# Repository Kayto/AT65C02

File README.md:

# AT65C02

**Latest News 15/12/2025**

**ATOS Software Released!** The main software suite for AT65C02 is now available in the Software_ATOS directory. ATOS (AT65C02 Operating System) provides a complete ROM-based monitor (SMON), interactive shell, trace/debugging commands, loadable program support, and integrated EhBASIC. The codebase has been extensively cleaned up and optimized with comprehensive documentation. This is now the recommended primary software for the AT65C02 platform.

**Hardware ideas 29/05/2025**

Picking up a few ideas for updates and improvements of the AT65C02.

1. How useful is the modem? Will i ever get around to testing this and integrating code? My vote is swinging to remove it. Opportunity to tidy the layout to better group a pinout for onboard rom programming.
2. I didn't add the possibility of using a MOS 6502! Looks like a simple jumper addition would allow this. 
3. The wireless UART doesnt have flow control - is there an alternative plug in wireless board that can provide this?
4. The HEX board resistor values...[sigh]!

**Previous News**
* **Minor fixes/additions to PCB to address some of the issues (see below revisions section).**
* **I am likely to pick up a futher revision 005 to address and consolidate some of the outstanding issues.**

## Introduction

Who doesn't want to build an 8 bit computer, if you don't, look away now.
I'm not a great coder or really an experienced maker but have enjoyed the magic of tinkering around with electronics since an early age. Whilst I have dabbled with 8 bit computing since the 80s, 40 years later I realise that I still do not really understand the inner workings of them. This project was to fill this knowledge gap.

Some of the best learning is obtained from example, making mistakes and getting your hands dirty. The only way for me is to actually break things down into individual steps, unpick the items then see how they all fit together and contribute.

I cant really credit myself with "designing" the AT65C02 - it borrows heavily from the work of others. However in breaking down these designs, incorporating changes and putting them together into my very own customised board, I have in many ways gained a much better understanding of how an 8 bit computer works. Result!

## Credits and thanks

Credits and thanks are worthy of being up front especially as I have leaned heavily on the work of others. Please follow the links to their respective documentation, they are far better at explaining and documenting than I can ever provide.

* <b>[Ben Eater's 8 bit computer](https://eater.net/8bit/)</b> \- the original inspiration\.
* <b>[Dawid Buchwald's](https://github.com/dbuchwald/6502)</b> DB6502 - this is brilliantly described and the designs form the basis for the AT65C02. The code examples and build environment are also the best for getting a solid base for coding. I recommend the github and [hackaday](https://hackaday.io/project/174128-db6502) report entries to really provide a deeper explanation of the design.
* <b>[Daryl Rictor](https://sbc.rictor.org/decoder.html)</b> \- for the DEC\-1 design\. The overall site also provides some great hobby computer examples\.
* <b>[AndersBNielsen](https://github.com/AndersBNielsen/SimpleModem)</b> for the "Simple Universal Modem" design.
* <b>[TEBL](https://github.com/tebl/C64-BlinkenDiag)</b> for the basis of the Blinkenlights.
* <b>[Michael Billington](https://github.com/mike42/6502-computer)</b> 65C02 computer - my first 65C02 build, super compact and a great starter for this journey.

## General Aims

* A 6502 build, as I am most familiar with this CPU and have at least a start at knowing some code and hardware requisities.
* Provide a learning platform for both the hardware and software. Ideally have a ready code base to get started with quickly.
* Avoid the hassles of masses of wiring and connections. To suit limited space, no mass of breadboards and able to tuck away in a cupboard to pick up quick.
* No great purist aspirations on the hardware, readily available components and no need to learn other code to get things running.

## Bespoke Aims

Some of these are really down to personal preference and perhaps held back a little by lack of knowledge.

* A load and save interface - to avoid pulling and burning ROMs every code example.
* Plenty of expansion - allows to tinker with interfacing displays and add ons.
* Wireless serial - the less wires the better.
* Adjustable memory decoder - because I can be indecisive and like to tinker.
* Blinkies - so I can get a real look at monitoring whats going on at an individual control signal, data and address line level.

## Final Features

In no particular order the main features in the final board are as follows.

* Onboard Step clock with manual and automatic tick. Speeds aprox 1-500Hz.
* Onboard 1mhz fixed clock.
* Seperate onboard serial clock.
* Blinky indicators - main signals, data and address, individual on/off switches.
* UART interface for external USB serial interface.
* ESP interface for wireless UART interface.
* Level shifter port for 5v and 3.3v signal conversion.
* Onboard 3.3v power regulator.
* Flexible IO and memory decoder via programable GAL. (this is now an add on board - it was too much to include on the same board).
* 2No VIAs - one for Keyboard, LCB and Blink LED - one spare for projects.
* Keyboard interface port (nice to have).
* LCD interface port.
* Onboard Blink LED (VIA1).
* VIA2 interface port.
* 4No. System Bus expansion interfaces (1No. via blinky latches).
* Modem audio interface.
* CPU extra signal breakout.
* LED brightness and LCD contrast adjusters - for late night blinky watching.
* Breakouts for ROM allow programming onboard via an Arduino or see below for ZIF option.
* Optional ZIF socket for ROM. Its a tight space but PCB ammended to accomodate the option of a ZIF socket at U8. **Please note that the ZIF socket interfers with the HEX expansion board. You will need a greater standoff to fit. The ZIF handle may also need shortening**.

## Memory Map

As will become clear when you tinker with 6502 builds, the hardware decisions up front impact the available memory size and locations.
Dawid Buchwald DB6502 provides a great explanation of the decisions around the choice of memory map and the differences with Ben Eater's design.
The default memory map for the AT65C02 is the same as DB6502 as follows.

| Segment | AT65C02 | Comment |
| ------- | ------- | ------- |
| RAM | 0x0000-0x7fff | 32K |
| VIA1 | 0x9000 | Connected to keyboard/LCD/blink LED |
| VIA2 | 0x8800 | VIA 2 port |
| ACIA | 0x8400 |  |
| ROM | 0xa000-0xffff | 24K First 8K of 32K ROM are not accessible |

Given I can be indecisive and to allow some experimentation with alternative memory maps I have included the option of switching to a programmable memory decoder. This uses the DEC-1 design by Daryl Rictor. The default DEC-1 map is as follows but with a bit of programming of the GALV22V10, you can experiment with other maps.

| Segment | DEC-1 | Comment |
| ------- | ----- | ------- |
| RAM | $0000-$01FF | zero page and stack space |
| IO Device #1 | $0200-$020F | (16 bytes) |
| IO Device #2 | $0210-$021F | (16 bytes) |
| IO Device #3 | $0220-$022F | (16 bytes) |
| IO Device #4 | $0230-$023F | (16 bytes) |
| Unassigned | $0240-$02FF |  |
| RAM | $0300-$7FFF | 32K |
| ROM | $8000-$FFFF | 32K |

## AT65C02 Build

The Final Rev004 PCB corrects the errors in my test builds. This first (Rev002) and second (Rev003) and third (Rev004) build was documented on [twitter](https://twitter.com/AdamT117). Feel free to check out those posts.

**Rev003 Spolier Alert** \- I had high hopes that Rev003 would be the final but alas things never work out as they should\, especially when learning\. Rev003 board undergoing testing\. ROM and VIA address decoding \- tested working\. RAM was troublesome\. I had a short between RAM OE and the RAM CS at the 74HC00 gates\. Oddly this was still there with all ICs unpopulated so must be a hidden short or trace damage\. The bare PCBs were ok\, so ruled that one out\. Given lack of time and parts I couldn't face another full build of a spare board\. Temporarily bodging the 74HC00 \(until i can find time to reassemble another board\)\, the Programmable memory decoder works when added to the dedicated expansion port\. Tested working alternative map with ROM at $8000\. OS/1 tested working via wireless serial add ons\. There is an issue on loading anything over 1K via wireless serial but this looks to be a software problem\.

**Rev002 Spolier alert** -The issues I found were mainly related to incorporating the adjustable address decoder. In trying to incorporate both a fixed and programmable GAL decoder I inadvertently bridged the RAM and ROM OE/CS lines. This was fixed with a trace cut and bodge but rendered the programmable memory decoder useless. Troubleshooting for the rev003 modifications involved temporary wires and jumpers. Other minor issues were silkscreen errors, this led me down a rabbit hole on a few occasions. The UART labels were mixed up, the level shifter pinout order was on the bottom of the board, the oscillator orientation was not clearly marked etc. I also took the opportunity to add in additional breakout headers for some unused CPU lines and for the ROM - allowing onboard ROM programming.

The repository provides the files for you to create your very own AT65C02.

* [Schematics](https://github.com/Kayto/blob/main/KiCad/Rev004/AT65C02_Schematic.pdf)
* [KiCad project files](https://github.com/Kayto/tree/main/KiCad/Rev004)
* [Gerber files](https://github.com/Kayto/tree/main/Gerbers)
* [BOM](https://github.com/Kayto/blob/main/KiCad/Rev004/AT_65C02_Computer_Rev004.csv)

### REVISION STATUS & ISSUES

**REV 004 - for final issue**

* Main board, Hex board and Programmable Memory Decoder Tested working.
* Modem - UNTESTED AT THE MOMENT

**Slight annoyances (which may or may not be investigated/fixed)**

* Hex board - for data FF the low F is very low brightness. It really needs some further balancing of the resistor values and grounding.
* Blinkies - Data lines have a bit of jitter with the clock. No biggie but OCD spotted it.
* Wireless Serial - using Xmodem is fine with very small code uploads but the larger files fail. Workaround is to use a wired serial. I am hoping this can be helped with code but might wait until I can acquire the skills to troubleshoot! **Update 06/2024. Rather stupidly I forgot that the ESP-01 does not have flow control. Therefore anything bigger than the buffer (like large file transfers) fails. The ESP-01 therefore provides a useful serial input but its use is limited.**
* Wired UART Interface - Silkscreen RTS and CTS need swapping. Bit of a mistake as I was looking at a direct FTDI plug in. As FTDI programmers vary its no big issue to use jumper wires. **Fixed 08/2023**.
* Wireless or wired serial switching - would have been nice to have a jumper to switch out the wireless ESP-01 module rather than unplugging. **Fixed 08/2023**.
* Breakouts for x2 spare level shifter channels. **Fixed 08/2023**.
* Standardise some headers to even sizes. **Fixed 08/2023**.

## JUMPERS

There are a number of jumpers/headers on the PCB which may need some explanation?
I have created a separate page [here](https://github.com/Kayto/blob/main/Jumpers.md) to explain them.

## Software

### ATOS - Primary Software Suite (RECOMMENDED)

**[Software_ATOS](https://github.com/Kayto/AT65C02/tree/main/Software/Software%20_ATOS)** is the main firmware and software suite for the AT65C02. It provides a complete operating environment with ROM-based SMON monitor, interactive shell, comprehensive debugging tools, and loadable program support.

**Key Features:**
- ROM-based SMON monitor with full debugging capabilities
- Interactive shell with command history
- Trace commands: single-step (TW), breakpoints (TB), run-to-address (TQ/TS)
- Loadable program support via Intel HEX format
- Integrated EhBASIC interpreter
- LCD and serial I/O drivers
- Multiple UART support (6551, 6522, 6850)
- Complete build system using Docker (cc65 toolchain)
- VS Code integration with build tasks

**Quick Start:**
```bash
cd Software_ATOS
docker run --rm -v '${PWD}:/mnt/project' dawidbuchwald/cc65-tools-make all
```

See the [ATOS README]([Software_ATOS](https://github.com/Kayto/AT65C02/tree/main/Software/Software%20_ATOS)/README.md) for complete documentation.

### Alternative Software Options

As stated earlier Dawid Buchwald provides a suite of ROM and loadable sources in his github repo. This will get you on your way to coding quickly. If you are struggling with a build environment then he also has great tutorial examples and even provides a [docker image](https://github.com/dbuchwald/cc65-tools), great work.

I am trying to avoid duplication of the original code repos so where possible will only include the new or revised code. Please check the original author licence included in the folders and in the acknowledgments.

| Reference | Description | Credit |
| --------- | ----------- | ------ |
| **[50\_mem\_read](https://github.com/Kayto/tree/main/Software/50_mem_read)** | RAM test, VIA1 and VIA 2 test blinks | by me - needs to be combined with the DB6502 repo for compilation. |
| **[sbc2os](https://github.com/Kayto/tree/main/Software/sbc2os)** | I include here the revised TASS source as it needed changes for the default AT65C02 memory map. A binary is also included for those who may struggle with TASS. | Original by [Daryl Rictor](https://sbc.rictor.org/sbcos.html). The original author README is included. |
| **[EhBasic](https://github.com/Kayto/tree/main/Software/EhBasic)** | Using the DB6502 docker image for compilation | Refer to the included [license](https://github.com/Kayto/blob/main/Software/EhBasic/LICENSE) file. |
| **[smon6502](https://github.com/Kayto/tree/main/Software/smon6502)** | [dhansel smon6502](https://github.com/dhansel/smon6502) Using the DB6502 VASM docker image for compilation. | Refer to the included [Readme](https://github.com/Kayto/blob/main/Software/smon6502/readme.md) file. |
| **[sysmon65](https://github.com/Kayto/tree/main/Software/SYSMON65-main)** | [jdimeglio sysmon65](https://github.com/jdimeglio/SYSMON65) | Binary only ATM. Will include the relevant modified source files shortly. Use original source and replace files that have been modified. Compilation requires the Michal Kowalski assembler/simulator |

The only other code requirement is for the ATTiny4313, for the onboard keyboard controller. An explanation of this is in the [Arduino](https://github.com/Kayto/tree/main/Software/Arduino) folder.

## Expansion

### Hex Board

Gerbers and KiCad is provided in this repo for an expansion board. This PCB plugs into the expansion port next to the blinkies. It provides hexidecmal display output aligned with the blinkenlights. Look in the software folder for the .jed files for programming the GALs.

### Programmable IO and memory decoder

This is now a seperate PCB that plugs into the relevant marked ports. Gerbers and KiCad provided. Allows tinkering with IO and memory maps. The design is based on the DEC-1 so refer to the links to Daryl Rictor's site for the .jed file for the GAL.

## Future Expansion

I have a number of aspirations for future expansion boards which are part way into development or at least have me thinking about. Most will rely on code development so really have no fixed date for release.

#### Floppy Drive controller

Allowing connection and control of a 5.25inch floppy disc drive. There are a few existing examples by some clever folk that could be adapted for use. I envisage a vertical board into an expansion slot - there are also plenty of additional breakouts on the AT65C02 that could be jumper wired if needed. A connector on an expansion board is not that robust. I thought of providing space for a DIN connector on the main board to serve this future item - but will save as just an idea for now.

#### Case

This could be an easy one as by some fluke the board size seems to fit some IKEA storage boxes I use. Most of the switches used on the board can be jumpered as I have used header pins. Similarily any expansion could be wired up too.

#### Debugger Plug-in

**Coming Soon -** A plug in board to allow degugging and onboard ROM programming via an Arduino.

## Licenses & acknowledgement

Further to the links in the credit section.
The design is an extension of Ben Eater's 6502 computer tutorial, which is itself based on the work of the 6502.org community.

**6502 KiCad Library**

The PCB files use modified versions of the 6502 KiCad Library. Copyright 2018, Nicholas Parks Young. All Rights Reserved. The 6502 KiCad Library library is licensed under the GNU LGPL v2.1

**EhBASIC**

With the exception of the files noted below, code base © 2021 Michael Billington, and is licensed under a Creative Commons Attribution 4.0 International License.
The files in EhBasic/basic/ are derived from EhBASIC, developed by Lee Davidson. The EhBASIC license allows for non-commerical use only. The most recent release and manual is hosted here, and a mirror of Lee's website can be found here.

EhBASIC is free but not copyright free. For non commercial use there is only one restriction, any derivative work should include, in any binary image distributed, the string "Derived from EhBASIC" and in any distribution that includes human readable files a file that includes the above string in a human readable form e.g. not as a comment in an HTML file.

**DB6502 Code**

OS/1, related code examples and Arduino code is Copyright (c) 2020 Dawid Buchwald and is licensed under a MIT License.

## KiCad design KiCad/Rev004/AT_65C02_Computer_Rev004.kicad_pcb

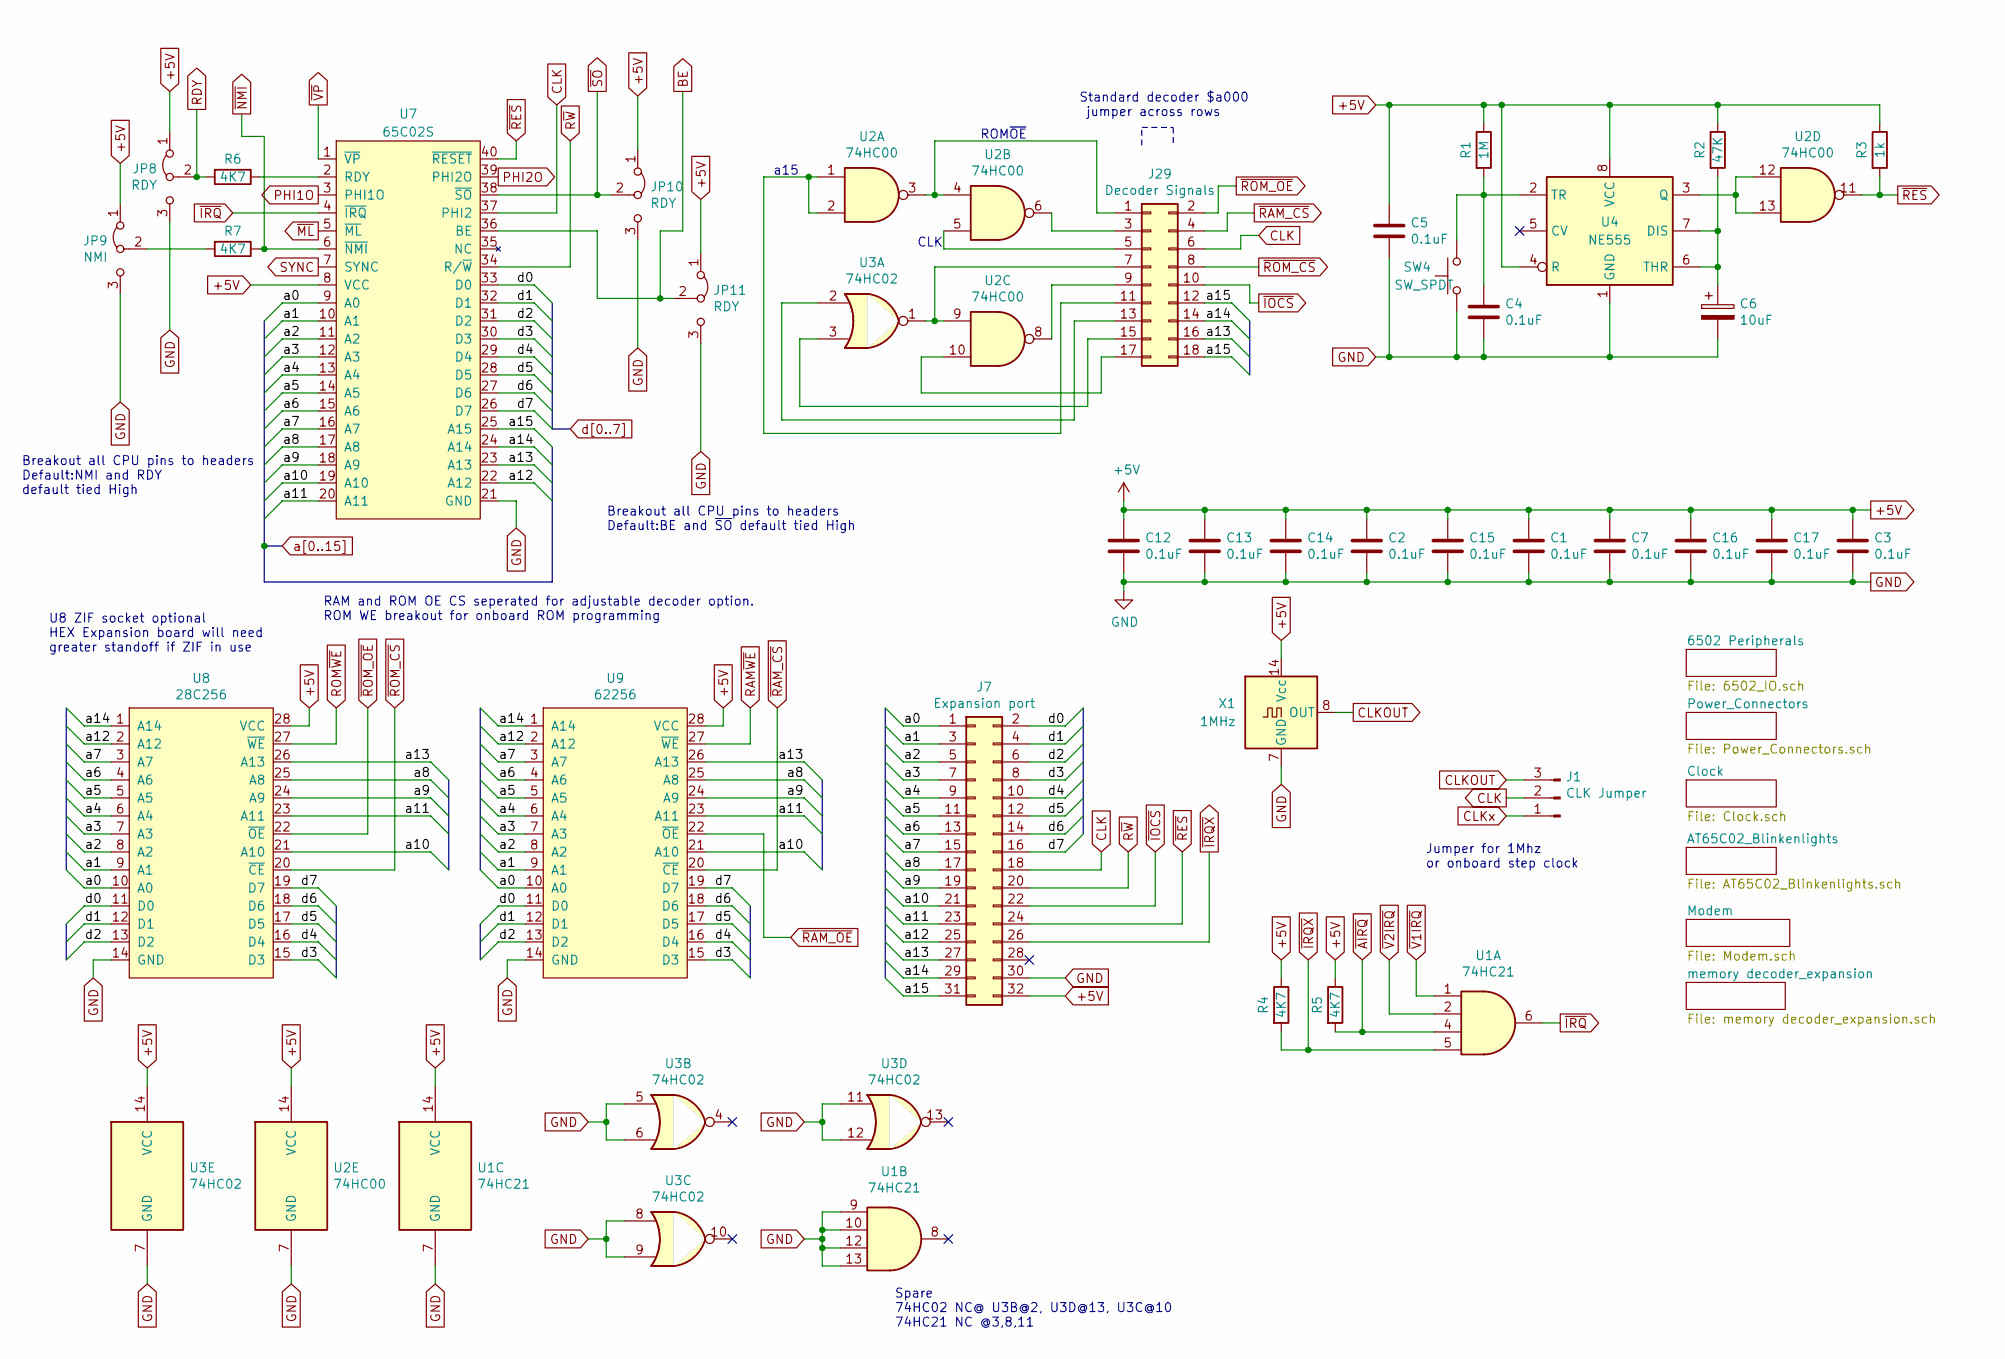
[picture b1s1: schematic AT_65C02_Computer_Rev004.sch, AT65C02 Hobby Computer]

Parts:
C1, C2, C3, C4, C5, C7, C12, C13, C14, C15, C16, C17: 0.1uF; C_Disc_D3.4mm_W2.1mm_P2.50mm
C6: 10uF; CP_Radial_D5.0mm_P2.50mm
J1: CLK Jumper; PinHeader_1x03_P2.54mm_Vertical
J7: Expansion port; PinSocket_2x16_P2.54mm_Vertical
J29: Decoder Signals; PinHeader_2x09_P2.54mm_Vertical
JP8, JP10, JP11: RDY; PinHeader_1x03_P2.54mm_Vertical
JP9: NMI; PinHeader_1x03_P2.54mm_Vertical
R1: 1M; R_Axial_DIN0207_L6.3mm_D2.5mm_P7.62mm_Horizontal
R2: 47K; R_Axial_DIN0207_L6.3mm_D2.5mm_P7.62mm_Horizontal
R3: 1k; R_Axial_DIN0207_L6.3mm_D2.5mm_P7.62mm_Horizontal
R4, R5, R6, R7: 4K7; R_Axial_DIN0207_L6.3mm_D2.5mm_P7.62mm_Horizontal
SW4: SW_SPDT; SW_PUSH_6mm
U1: 74HC21; DIP-14_W7.62mm_Socket
U2: 74HC00; DIP-14_W7.62mm_Socket
U3: 74HC02; DIP-14_W7.62mm_Socket
U4: NE555; DIP-8_W7.62mm_Socket
U7: 65C02S; DIP-40_W15.24mm_Socket
U8: 28C256; DIP_Socket-28_W11.9_W12.7_W15.24_W17.78_W18.5_3M_228-1277-0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
U9: 62256; DIP-28_W15.24mm_Socket
X1: 1MHz; Oscillator_DIP-14

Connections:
BE: JP11.2 (C), U7.36 (BE); also elsewhere on the board
CLK: J1.2, J7.18, J29.6, U7.37 (PHI2); also elsewhere on the board
CLKOUT: J1.3, X1.8 (OUT)
CLKx: J1.1; also elsewhere on the board
unnamed: C4.1, R1.2, SW4.2, U4.2 (TR)
unnamed: C6.1, R2.2, U4.6 (THR), U4.7 (DIS)
unnamed: J29.1, U2.3, U2.4
unnamed: J29.3, U2.6
unnamed: J29.5, U2.5
unnamed: J29.7, U2.9, U3.1
unnamed: J29.9, U2.8
unnamed: J29.11, U2.1, U2.2
unnamed: J29.13, U3.2
unnamed: J29.15, U3.3
unnamed: J29.17, U2.10
unnamed: JP9.2 (C), R7.2
unnamed: R6.1, U7.2 (RDY)
unnamed: U2.12, U2.13, U4.3 (Q)
PHI1O: U7.3 (PHI1O); also elsewhere on the board
PHI2O: U7.39 (PHI2O); also elsewhere on the board
RAM~WE~: U9.27 (~WE); also elsewhere on the board
RDY: JP8.2 (C), R6.2; also elsewhere on the board
ROM~WE: U8.27 (~WE); also elsewhere on the board
R~W: J7.20, U7.34 (R/~W); also elsewhere on the board
SYNC: U7.7 (SYNC); also elsewhere on the board
a0: J7.1, U7.9 (A0), U8.10 (A0), U9.10 (A0); also elsewhere on the board
a1: J7.3, U7.10 (A1), U8.9 (A1), U9.9 (A1); also elsewhere on the board
a2: J7.5, U7.11 (A2), U8.8 (A2), U9.8 (A2); also elsewhere on the board
a3: J7.7, U7.12 (A3), U8.7 (A3), U9.7 (A3); also elsewhere on the board
a4: J7.9, U7.13 (A4), U8.6 (A4), U9.6 (A4); also elsewhere on the board
a5: J7.11, U7.14 (A5), U8.5 (A5), U9.5 (A5); also elsewhere on the board
a6: J7.13, U7.15 (A6), U8.4 (A6), U9.4 (A6); also elsewhere on the board
a7: J7.15, U7.16 (A7), U8.3 (A7), U9.3 (A7); also elsewhere on the board
a8: J7.17, U7.17 (A8), U8.25 (A8), U9.25 (A8); also elsewhere on the board
a9: J7.19, U7.18 (A9), U8.24 (A9), U9.24 (A9); also elsewhere on the board
a10: J7.21, U7.19 (A10), U8.21 (A10), U9.21 (A10); also elsewhere on the board
a11: J7.23, U7.20 (A11), U8.23 (A11), U9.23 (A11); also elsewhere on the board
a12: J7.25, U7.22 (A12), U8.2 (A12), U9.2 (A12); also elsewhere on the board
a13: J7.27, J29.16, U7.23 (A13), U8.26 (A13), U9.26 (A13); also elsewhere on the board
a14: J7.29, J29.14, U7.24 (A14), U8.1 (A14), U9.1 (A14); also elsewhere on the board
a15: J7.31, J29.12, J29.18, U7.25 (A15); also elsewhere on the board
d0: J7.2, U7.33 (D0), U8.11 (D0), U9.11 (D0); also elsewhere on the board
d1: J7.4, U7.32 (D1), U8.12 (D1), U9.12 (D1); also elsewhere on the board
d2: J7.6, U7.31 (D2), U8.13 (D2), U9.13 (D2); also elsewhere on the board
d3: J7.8, U7.30 (D3), U8.15 (D3), U9.15 (D3); also elsewhere on the board
d4: J7.10, U7.29 (D4), U8.16 (D4), U9.16 (D4); also elsewhere on the board
d5: J7.12, U7.28 (D5), U8.17 (D5), U9.17 (D5); also elsewhere on the board
d6: J7.14, U7.27 (D6), U8.18 (D6), U9.18 (D6); also elsewhere on the board
d7: J7.16, U7.26 (D7), U8.19 (D7), U9.19 (D7); also elsewhere on the board
~AIRQ: R5.2, U1.4; also elsewhere on the board
~IOCS: J7.22, J29.10; also elsewhere on the board
~IRQ: U1.6, U7.4 (~IRQ); also elsewhere on the board
~IRQX: J7.26, R4.2, U1.5; also elsewhere on the board
~ML: U7.5 (~ML); also elsewhere on the board
~NMI: R7.1, U7.6 (~NMI); also elsewhere on the board
~RAM_CS: J29.4, U9.20 (~CE); also elsewhere on the board
~RAM_OE: U9.22 (~OE); also elsewhere on the board
~RES: J7.24, R3.2, U2.11, U7.40 (~RESET); also elsewhere on the board
~ROM_CS: J29.8, U8.20 (~CE); also elsewhere on the board
~ROM_OE: J29.2, U8.22 (~OE); also elsewhere on the board
~SO: JP10.2 (C), U7.38 (~SO); also elsewhere on the board
~V1IRQ: U1.1; also elsewhere on the board
~V2IRQ: U1.2; also elsewhere on the board
~VP: U7.1 (~VP); also elsewhere on the board

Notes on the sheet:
Breakout all CPU pins to headers Default:NMI and RDY default tied High
RAM and ROM OE CS seperated for adjustable decoder option. ROM WE breakout for onboard ROM programming
Jumper for 1Mhz or onboard step clock
Spare 74HC02 NC@ U3B@2, U3D@13, U3C@10 74HC21 NC @3,8,11
Standard decoder $a000 jumper across rows
Breakout all CPU pins to headers Default:BE and ~SO~ default tied High
U8 ZIF socket optional HEX Expansion board will need greater standoff if ZIF in use
ROM~OE
a15
CLK

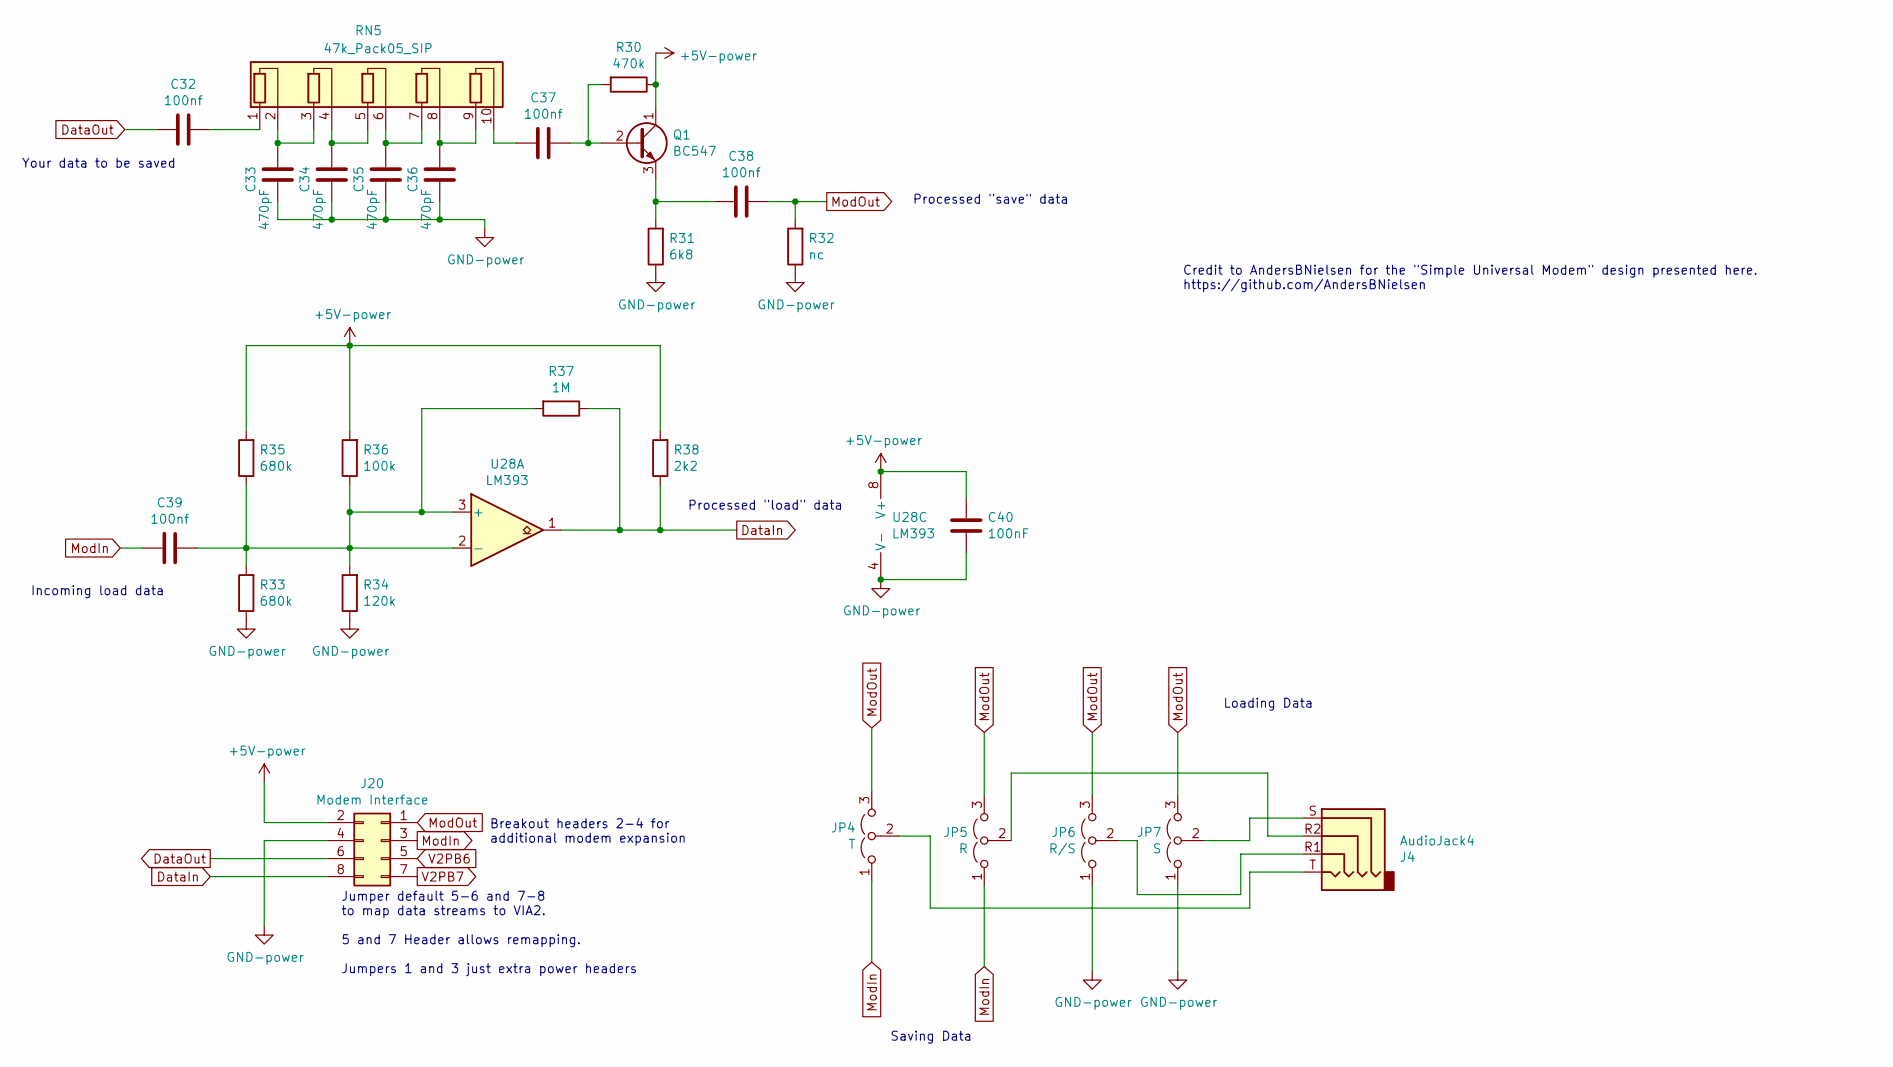
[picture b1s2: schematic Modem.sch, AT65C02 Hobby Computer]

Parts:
C32, C37, C38, C39: 100nf; C_Disc_D3.4mm_W2.1mm_P2.50mm
C33, C34, C35, C36: 470pF; C_Disc_D3.4mm_W2.1mm_P2.50mm
C40: 100nF; C_Disc_D3.4mm_W2.1mm_P2.50mm
J4: AudioJack4; Jack_3.5mm_PJ320E_Horizontal
J20: Modem Interface; PinSocket_2x04_P2.54mm_Vertical
JP4: T; PinHeader_1x03_P2.54mm_Vertical
JP5: R; PinHeader_1x03_P2.54mm_Vertical
JP6: R/S; PinHeader_1x03_P2.54mm_Vertical
JP7: S; PinHeader_1x03_P2.54mm_Vertical
Q1: BC547; TO-92_Inline
R30: 470k; R_Axial_DIN0207_L6.3mm_D2.5mm_P7.62mm_Horizontal
R31: 6k8; R_Axial_DIN0207_L6.3mm_D2.5mm_P7.62mm_Horizontal
R32: nc; R_Axial_DIN0207_L6.3mm_D2.5mm_P7.62mm_Horizontal
R33, R35: 680k; R_Axial_DIN0207_L6.3mm_D2.5mm_P7.62mm_Horizontal
R34: 120k; R_Axial_DIN0207_L6.3mm_D2.5mm_P7.62mm_Horizontal
R36: 100k; R_Axial_DIN0207_L6.3mm_D2.5mm_P7.62mm_Horizontal
R37: 1M; R_Axial_DIN0207_L6.3mm_D2.5mm_P7.62mm_Horizontal
R38: 2k2; R_Axial_DIN0207_L6.3mm_D2.5mm_P7.62mm_Horizontal
RN5: 47k_Pack05_SIP; R_Array_SIP10
U28: LM393; DIP-8_W7.62mm_Socket

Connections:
DataIn: J20.8, R37.1, R38.1, U28.1
DataOut: C32.2, J20.6
ModIn: C39.2, J20.3, JP4.1 (A), JP5.1 (A)
ModOut: C38.1, J20.1, JP4.3 (B), JP5.3 (B), JP6.3 (B), JP7.3 (B), R32.2
unnamed: C32.1, RN5.1 (R1.1)
unnamed: C33.2, RN5.2 (R1.2), RN5.3 (R2.1)
unnamed: C34.2, RN5.4 (R2.2), RN5.5 (R3.1)
unnamed: C35.2, RN5.6 (R3.2), RN5.7 (R4.1)
unnamed: C36.2, RN5.8 (R4.2), RN5.9 (R5.1)
unnamed: C37.1, Q1.2 (B), R30.2
unnamed: C37.2, RN5.10 (R5.2)
unnamed: C38.2, Q1.3 (E), R31.2
unnamed: C39.1, R33.2, R34.2, R35.1, R36.1, R37.2, U28.2 (-), U28.3 (+)
unnamed: J4.R1, JP6.2 (C)
unnamed: J4.R2, JP5.2 (C)
unnamed: J4.S, JP7.2 (C)
unnamed: J4.T, JP4.2 (C)
V2PB6: J20.5; also elsewhere on the board
V2PB7: J20.7; also elsewhere on the board

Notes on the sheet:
Credit to AndersBNielsen for the "Simple Universal Modem" design presented here. https://github.com/AndersBNielsen
Loading Data
Saving Data
Breakout headers 2-4 for additional modem expansion
Jumper default 5-6 and 7-8 to map data streams to VIA2. 5 and 7 Header allows remapping. Jumpers 1 and 3 just extra power headers
Processed "load" data
Processed "save" data
Your data to be saved
Incoming load data

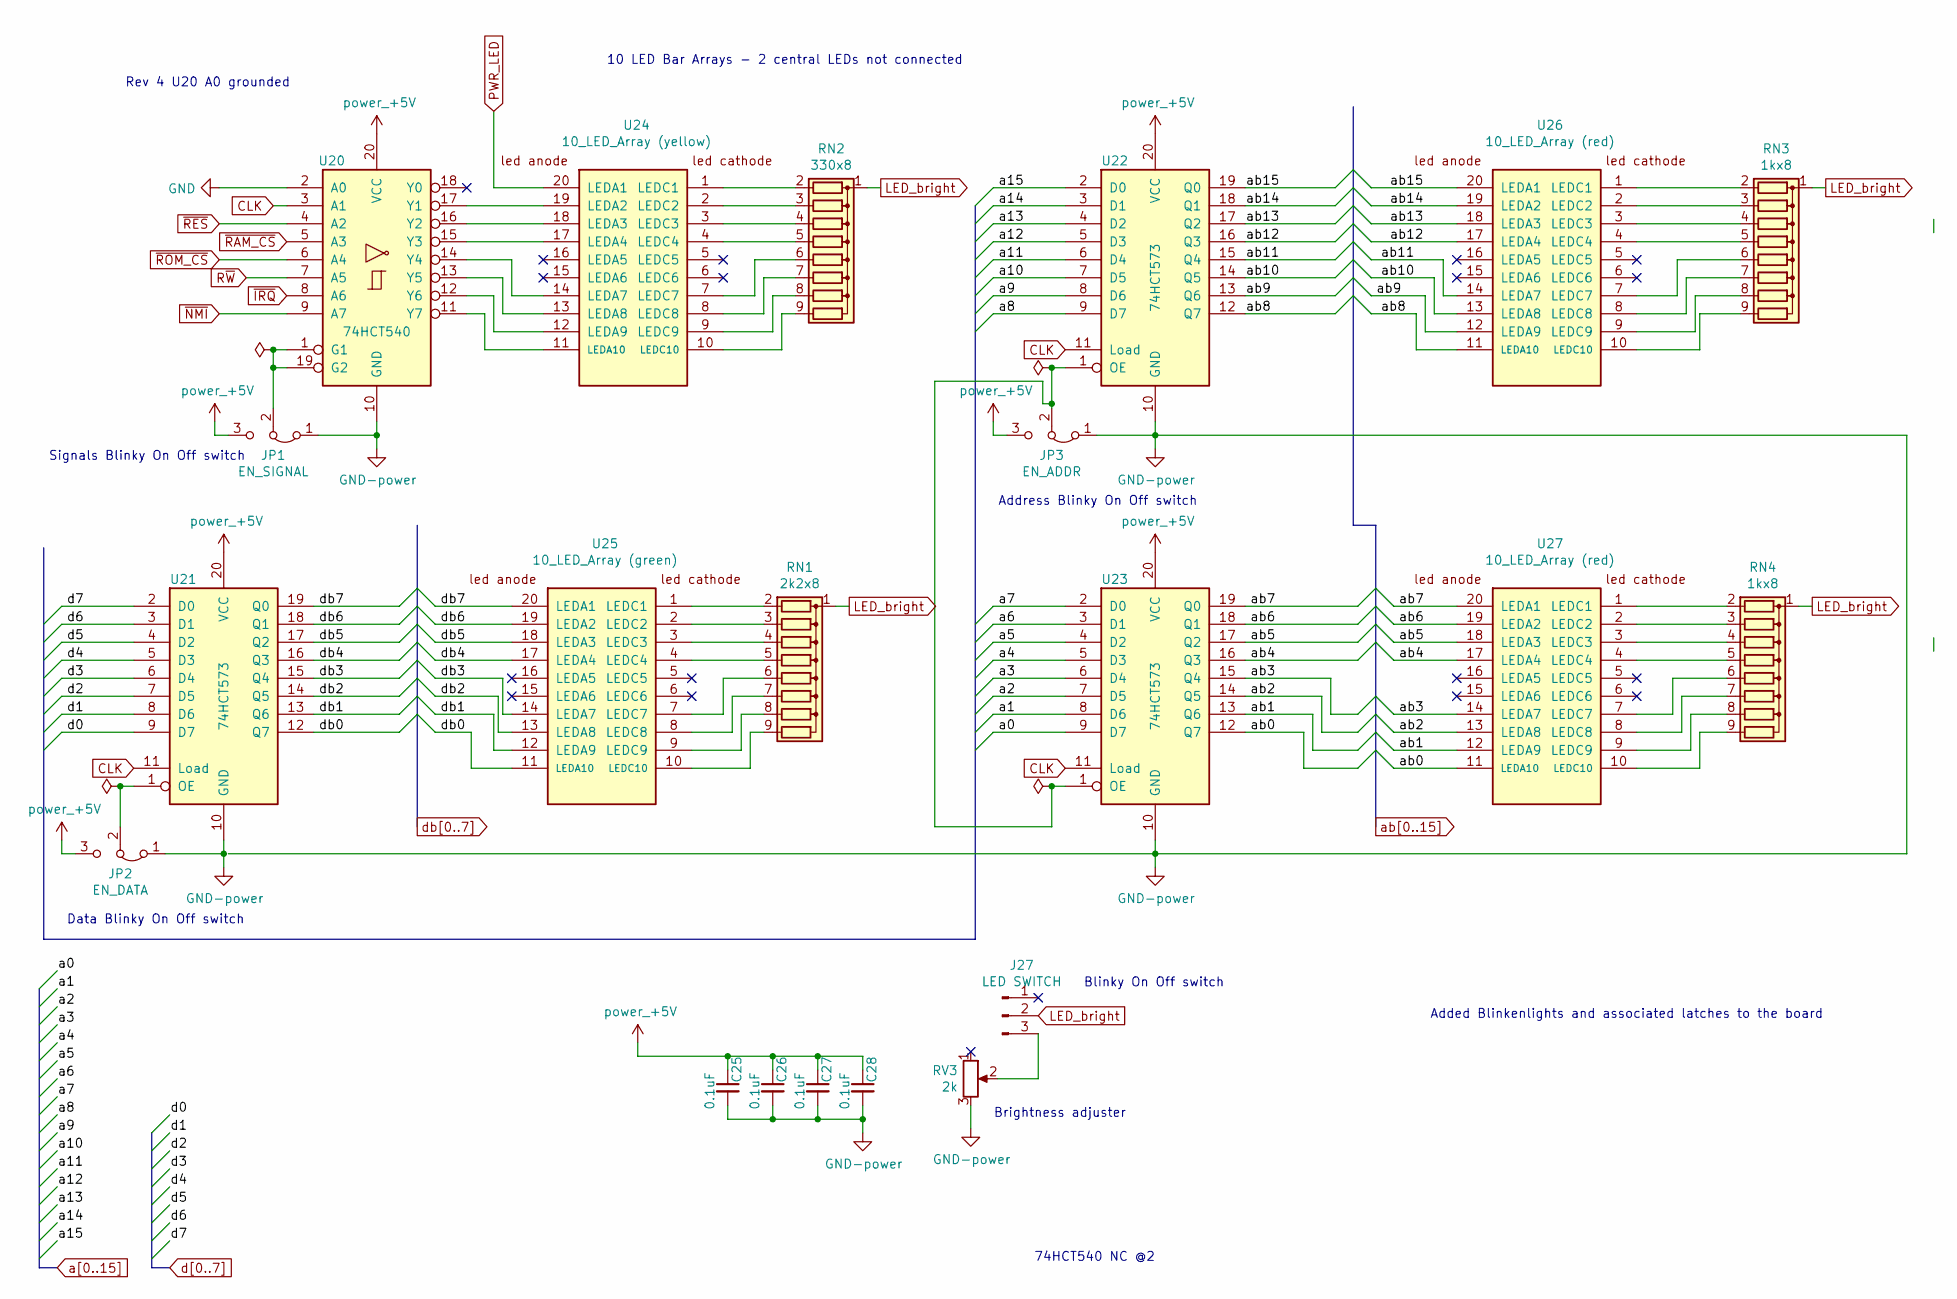
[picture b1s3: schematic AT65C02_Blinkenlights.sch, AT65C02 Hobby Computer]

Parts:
C25, C26, C27, C28: 0.1uF; C_Disc_D3.4mm_W2.1mm_P2.50mm
J27: LED SWITCH; PinHeader_1x03_P2.54mm_Vertical
JP1: EN_SIGNAL; PinHeader_1x03_P2.54mm_Vertical
JP2: EN_DATA; PinHeader_1x03_P2.54mm_Vertical
JP3: EN_ADDR; PinHeader_1x03_P2.54mm_Vertical
RN1: 2k2x8; R_Array_SIP9
RN2: 330x8; R_Array_SIP9
RN3, RN4: 1kx8; R_Array_SIP9
RV3: 2k; Potentiometer_Piher_PT-10-V10_Vertical
U20: 74HCT540; DIP-20_W7.62mm_Socket_LongPads
U21, U22, U23: 74HCT573; DIP-20_W7.62mm_Socket_LongPads
U24: 10_LED_Array (yellow); DIP-20_W7.62mm_Socket
U25: 10_LED_Array (green); DIP-20_W7.62mm_Socket
U26, U27: 10_LED_Array (red); DIP-20_W7.62mm_Socket

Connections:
CLK: U20.3 (A1), U21.11 (Load), U22.11 (Load), U23.11 (Load); also elsewhere on the board
LED_bright: J27.2, RN1.1 (common), RN2.1 (common), RN3.1 (common), RN4.1 (common)
unnamed: J27.3, RV3.2
unnamed: JP1.2 (C), U20.1 (G1), U20.19 (G2)
unnamed: JP2.2 (C), U21.1 (OE)
unnamed: JP3.2 (C), U22.1 (OE), U23.1 (OE)
unnamed: RN1.2 (R1), U25.1 (LEDC1)
unnamed: RN1.3 (R2), U25.2 (LEDC2)
unnamed: RN1.4 (R3), U25.3 (LEDC3)
unnamed: RN1.5 (R4), U25.4 (LEDC4)
unnamed: RN1.6 (R5), U25.7 (LEDC7)
unnamed: RN1.7 (R6), U25.8 (LEDC8)
unnamed: RN1.8 (R7), U25.9 (LEDC9)
unnamed: RN1.9 (R8), U25.10 (LEDC10)
unnamed: RN2.2 (R1), U24.1 (LEDC1)
unnamed: RN2.3 (R2), U24.2 (LEDC2)
unnamed: RN2.4 (R3), U24.3 (LEDC3)
unnamed: RN2.5 (R4), U24.4 (LEDC4)
unnamed: RN2.6 (R5), U24.7 (LEDC7)
unnamed: RN2.7 (R6), U24.8 (LEDC8)
unnamed: RN2.8 (R7), U24.9 (LEDC9)
unnamed: RN2.9 (R8), U24.10 (LEDC10)
unnamed: RN3.2 (R1), U26.1 (LEDC1)
unnamed: RN3.3 (R2), U26.2 (LEDC2)
unnamed: RN3.4 (R3), U26.3 (LEDC3)
unnamed: RN3.5 (R4), U26.4 (LEDC4)
unnamed: RN3.6 (R5), U26.7 (LEDC7)
unnamed: RN3.7 (R6), U26.8 (LEDC8)
unnamed: RN3.8 (R7), U26.9 (LEDC9)
unnamed: RN3.9 (R8), U26.10 (LEDC10)
unnamed: RN4.2 (R1), U27.1 (LEDC1)
unnamed: RN4.3 (R2), U27.2 (LEDC2)
unnamed: RN4.4 (R3), U27.3 (LEDC3)
unnamed: RN4.5 (R4), U27.4 (LEDC4)
unnamed: RN4.6 (R5), U27.7 (LEDC7)
unnamed: RN4.7 (R6), U27.8 (LEDC8)
unnamed: RN4.8 (R7), U27.9 (LEDC9)
unnamed: RN4.9 (R8), U27.10 (LEDC10)
unnamed: U20.11 (Y7), U24.11 (LEDA10)
unnamed: U20.12 (Y6), U24.12 (LEDA9)
unnamed: U20.13 (Y5), U24.13 (LEDA8)
unnamed: U20.14 (Y4), U24.14 (LEDA7)
unnamed: U20.15 (Y3), U24.17 (LEDA4)
unnamed: U20.16 (Y2), U24.18 (LEDA3)
unnamed: U20.17 (Y1), U24.19 (LEDA2)
R~W: U20.7 (A5); also elsewhere on the board
a0: U23.9 (D7); also elsewhere on the board
a1: U23.8 (D6); also elsewhere on the board
a2: U23.7 (D5); also elsewhere on the board
a3: U23.6 (D4); also elsewhere on the board
a4: U23.5 (D3); also elsewhere on the board
a5: U23.4 (D2); also elsewhere on the board
a6: U23.3 (D1); also elsewhere on the board
a7: U23.2 (D0); also elsewhere on the board
a8: U22.9 (D7); also elsewhere on the board
a9: U22.8 (D6); also elsewhere on the board
a10: U22.7 (D5); also elsewhere on the board
a11: U22.6 (D4); also elsewhere on the board
a12: U22.5 (D3); also elsewhere on the board
a13: U22.4 (D2); also elsewhere on the board
a14: U22.3 (D1); also elsewhere on the board
a15: U22.2 (D0); also elsewhere on the board
ab0: U23.12 (Q7), U27.11 (LEDA10); also elsewhere on the board
ab1: U23.13 (Q6), U27.12 (LEDA9); also elsewhere on the board
ab2: U23.14 (Q5), U27.13 (LEDA8); also elsewhere on the board
ab3: U23.15 (Q4), U27.14 (LEDA7); also elsewhere on the board
ab4: U23.16 (Q3), U27.17 (LEDA4); also elsewhere on the board
ab5: U23.17 (Q2), U27.18 (LEDA3); also elsewhere on the board
ab6: U23.18 (Q1), U27.19 (LEDA2); also elsewhere on the board
ab7: U23.19 (Q0), U27.20 (LEDA1); also elsewhere on the board
ab8: U22.12 (Q7), U26.11 (LEDA10); also elsewhere on the board
ab9: U22.13 (Q6), U26.12 (LEDA9); also elsewhere on the board
ab10: U22.14 (Q5), U26.13 (LEDA8); also elsewhere on the board
ab11: U22.15 (Q4), U26.14 (LEDA7); also elsewhere on the board
ab12: U22.16 (Q3), U26.17 (LEDA4); also elsewhere on the board
ab13: U22.17 (Q2), U26.18 (LEDA3); also elsewhere on the board
ab14: U22.18 (Q1), U26.19 (LEDA2); also elsewhere on the board
ab15: U22.19 (Q0), U26.20 (LEDA1); also elsewhere on the board
d0: U21.9 (D7); also elsewhere on the board
d1: U21.8 (D6); also elsewhere on the board
d2: U21.7 (D5); also elsewhere on the board
d3: U21.6 (D4); also elsewhere on the board
d4: U21.5 (D3); also elsewhere on the board
d5: U21.4 (D2); also elsewhere on the board
d6: U21.3 (D1); also elsewhere on the board
d7: U21.2 (D0); also elsewhere on the board
db0: U21.12 (Q7), U25.11 (LEDA10); also elsewhere on the board
db1: U21.13 (Q6), U25.12 (LEDA9); also elsewhere on the board
db2: U21.14 (Q5), U25.13 (LEDA8); also elsewhere on the board
db3: U21.15 (Q4), U25.14 (LEDA7); also elsewhere on the board
db4: U21.16 (Q3), U25.17 (LEDA4); also elsewhere on the board
db5: U21.17 (Q2), U25.18 (LEDA3); also elsewhere on the board
db6: U21.18 (Q1), U25.19 (LEDA2); also elsewhere on the board
db7: U21.19 (Q0), U25.20 (LEDA1); also elsewhere on the board
~IRQ: U20.8 (A6); also elsewhere on the board
~NMI: U20.9 (A7); also elsewhere on the board
~RAM_CS: U20.5 (A3); also elsewhere on the board
~RES: U20.4 (A2); also elsewhere on the board
~ROM_CS: U20.6 (A4); also elsewhere on the board

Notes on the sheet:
Added Blinkenlights and associated latches to the board
Brightness adjuster
Blinky On Off switch
10 LED Bar Arrays - 2 central LEDs not connected
Data Blinky On Off switch
Signals Blinky On Off switch
Address Blinky On Off switch
74HCT540 NC @2
Rev 4 U20 A0 grounded

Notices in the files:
README.md:
Licenses & acknowledgement:
Further to the links in the credit section.
The design is an extension of Ben Eater's 6502 computer tutorial, which is itself based on the work of the 6502.org community.
6502 KiCad Library
The PCB files use modified versions of the 6502 KiCad Library. Copyright 2018, Nicholas Parks Young. All Rights Reserved. The 6502 KiCad Library library is licensed under the GNU LGPL v2.1
EhBASIC
With the exception of the files noted below, code base © 2021 Michael Billington, and is licensed under a Creative Commons Attribution 4.0 International License.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
